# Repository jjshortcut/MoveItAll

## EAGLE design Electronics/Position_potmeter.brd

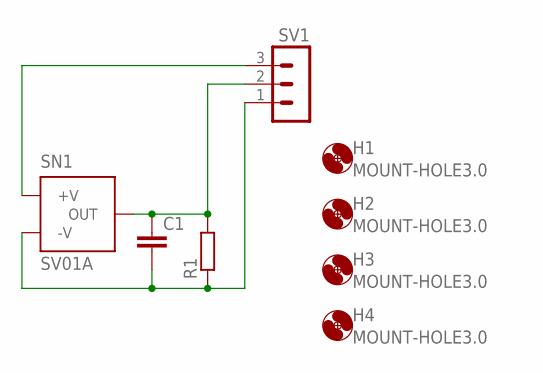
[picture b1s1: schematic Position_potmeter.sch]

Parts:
C1: C-EUC0805K; C0805K
H1, H2, H3, H4: MOUNT-HOLE3.0; 3,0
R1: R-EU_M0805; M0805
SN1: SV01A
SV1: MA03-1

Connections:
unnamed: SN1.3 (+V), SV1.3
unnamed: C1.1, R1.2, SN1.2 (OUT), SV1.2
unnamed: C1.2, R1.1, SN1.1 (-V), SV1.1

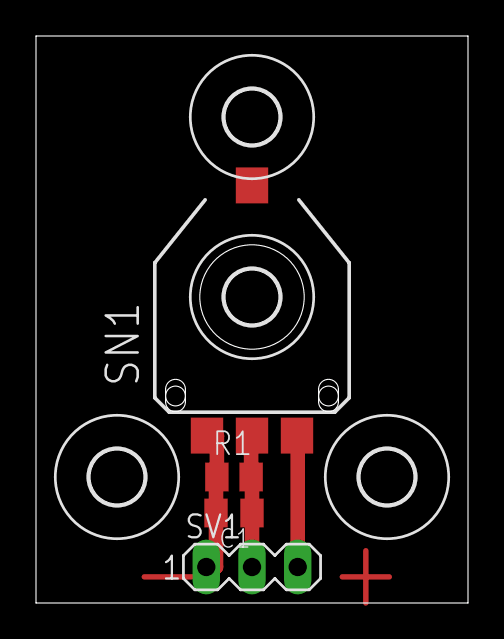
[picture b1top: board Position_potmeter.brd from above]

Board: 2 copper layers, 24.0 x 31.5 mm, 8 parts (0 on the bottom side), 3 nets.

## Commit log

2018-01-21 Init
2018-01-21 Todo added
2018-01-23 HMI mockup added for nextion 2.4"lcd
2018-01-24 HMI updated Code made working, P controller working with HMI
2018-01-31 Added X=<nr of times> auto movement, not finished, todo!
2018-01-31 pwm control is not changed to on/off since its not necassary and causes noise (hearable)
2018-01-31 X=times auto movement now first initial version working correctly
2018-01-31 Working, some fixes/prevent stuff
2018-01-31 no message
2018-02-02 Cleaned up code Added current overflow status
2018-02-04 Added current peak timeout current overflow, shuts down movement after x ms (to be tested)
2018-02-05 Enclosure around gears/motor added
2018-02-07 Ready V1 version for delivery day
2018-02-07 manual added
2018-02-15 U (up 500ms) and D (down 500ms) command added for 500ms motor rotation (future use and untanglement) Added some stuff to prevent movement during releasing the hand movement (to be tested!!!) added un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
2018-05-30 Latest
